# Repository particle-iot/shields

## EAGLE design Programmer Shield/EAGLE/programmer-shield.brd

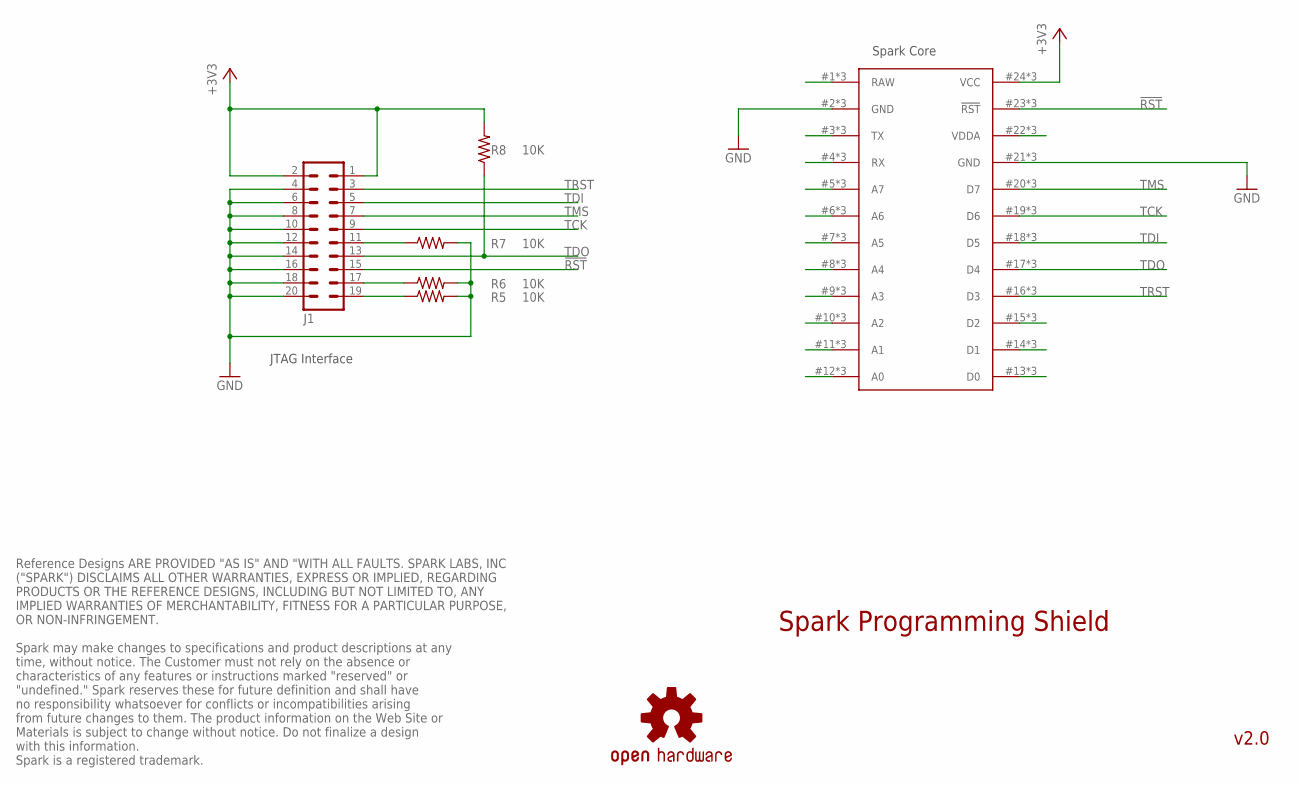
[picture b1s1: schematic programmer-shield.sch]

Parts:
J1: ML20
LOGO1: OSHW-LOGOM; OSHW-LOGO-M
R5, R6, R7, R8: 10K; AXIAL-0.3
U$1: SPARK_CORE; SPARK_CORE_STACKABLE

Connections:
!RST: J1.15, U$1.23 (!RST), U$1.#23 (!RST), U$1.@23 (!RST)
+3V3: J1.1, J1.2, R8.P$2 (2), U$1.24 (VCC), U$1.#24 (VCC), U$1.@24 (VCC)
GND: J1.4, J1.6, J1.8, J1.10, J1.12, J1.14, J1.16, J1.18, J1.20, R5.P$2 (2), R6.P$2 (2), R7.P$2 (2), U$1.2 (GND), U$1.21 (GND), U$1.#2 (GND), U$1.#21 (GND), U$1.@2 (GND), U$1.@21 (GND)
unnamed: U$1.1 (RAW), U$1.#1 (RAW), U$1.@1 (RAW)
unnamed: U$1.3 (TX), U$1.#3 (TX), U$1.@3 (TX)
unnamed: U$1.4 (RX), U$1.#4 (RX), U$1.@4 (RX)
unnamed: U$1.5 (A7), U$1.#5 (A7), U$1.@5 (A7)
unnamed: U$1.6 (A6), U$1.#6 (A6), U$1.@6 (A6)
unnamed: U$1.7 (A5), U$1.#7 (A5), U$1.@7 (A5)
unnamed: U$1.8 (A4), U$1.#8 (A4), U$1.@8 (A4)
unnamed: U$1.9 (A3), U$1.#9 (A3), U$1.@9 (A3)
unnamed: U$1.10 (A2), U$1.#10 (A2), U$1.@10 (A2)
unnamed: U$1.11 (A1), U$1.#11 (A1), U$1.@11 (A1)
unnamed: U$1.12 (A0), U$1.#12 (A0), U$1.@12 (A0)
unnamed: U$1.13 (D0), U$1.#13 (D0), U$1.@13 (D0)
unnamed: J1.19, R5.P$1 (1)
unnamed: J1.17, R6.P$1 (1)
unnamed: J1.11, R7.P$1 (1)
unnamed: U$1.14 (D1), U$1.#14 (D1), U$1.@14 (D1)
unnamed: U$1.15 (D2), U$1.#15 (D2), U$1.@15 (D2)
unnamed: U$1.22 (VDDA), U$1.#22 (VDDA), U$1.@22 (VDDA)
TCK: J1.9, U$1.19 (D6), U$1.#19 (D6), U$1.@19 (D6)
TDI: J1.5, U$1.18 (D5), U$1.#18 (D5), U$1.@18 (D5)
TDO: J1.13, R8.P$1 (1), U$1.17 (D4), U$1.#17 (D4), U$1.@17 (D4)
TMS: J1.7, U$1.20 (D7), U$1.#20 (D7), U$1.@20 (D7)
TRST: J1.3, U$1.16 (D3), U$1.#16 (D3), U$1.@16 (D3)

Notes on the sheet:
JTAG Interface
Spark Core
Spark Programming Shield
v2.0
Reference Designs ARE PROVIDED "AS IS" AND "WITH ALL FAULTS. SPARK LABS, INC ("SPARK") DISCLAIMS ALL OTHER WARRANTIES, EXPRESS OR IMPLIED, REGARDING PRODUCTS OR THE REFERENCE DESIGNS, INCLUDING BUT NOT LIMITED TO, ANY IMPLIED WARRANTIES OF MERCHANTABILITY, FITNESS FOR A PARTICULAR PURPOSE, OR NON-I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

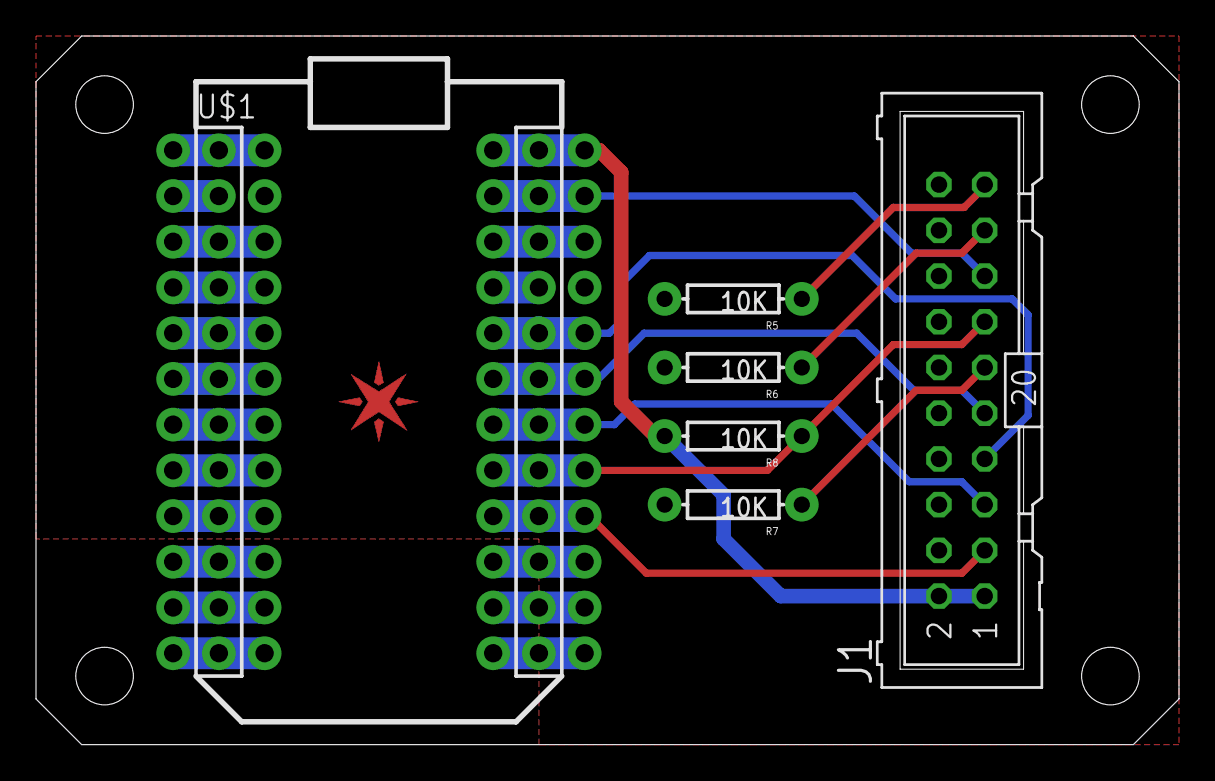
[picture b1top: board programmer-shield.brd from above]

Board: 2 copper layers, 63.5 x 39.4 mm, 8 parts (1 on the bottom side), 26 nets.

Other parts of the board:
E$1: SPARK_LOGO_PLUS_PLANE

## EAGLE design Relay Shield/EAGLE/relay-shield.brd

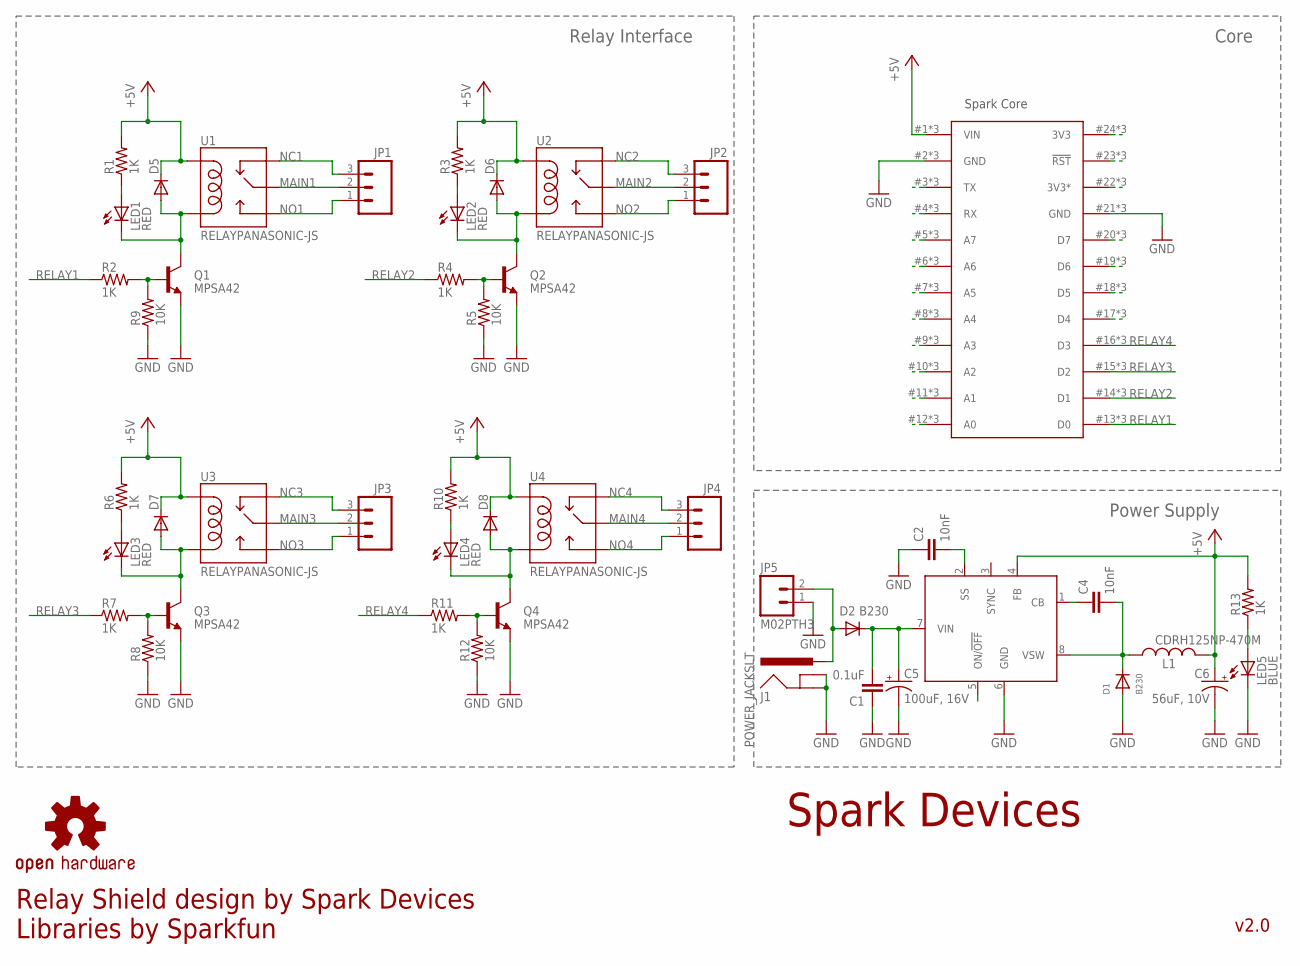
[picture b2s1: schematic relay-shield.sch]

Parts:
C1: 0.1uF; 0603-CAP
C2, C4: 10nF; 0603-CAP
C5: 100uF, 16V; PANASONIC_D
C6: 56uF, 10V; PANASONIC_D
D1, D2: B230; SMADIODE
D5, D6, D7, D8: DIODE-SOD123; SOD123
J1: POWER_JACKSLT; POWER_JACK_SLOT
JP1, JP2, JP3, JP4: M03-SCREW-5MM; SCREWTERMINAL-5MM-3
JP5: M02PTH3; 1X02_LONGPADS
L1: CDRH125NP-470M; CDRH125
LED1, LED2, LED3, LED4: RED; LED-0603
LED5: BLUE; LED-0603
LOGO1: OSHW-LOGOM; OSHW-LOGO-M
Q1, Q2, Q3, Q4: MPSA42; SOT23
R1, R2, R3, R4, R6, R7, R10, R11, R13: 1K; 0603-RES
R5, R8, R9, R12: 10K; 0603-RES
U1, U2, U3, U4: RELAYPANASONIC-JS; JS1-5V-F
U6: LM2672; SO08
U$1: SPARK_CORE; SPARK_CORE_STACKABLE

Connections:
+5V: C6.+, D5.C, D6.C, D7.C, D8.C, L1.2, R1.2, R3.2, R6.2, R10.2, R13.2, U1.COIL1, U2.COIL1, U3.COIL1, U4.COIL1, U6.4 (FB), U$1.1 (VIN), U$1.#1 (VIN), U$1.@1 (VIN)
GND: C1.1, C2.1, C5.-, C6.-, D1.A, J1.GND@1 (GNDBREAK), J1.GND@2 (GND), JP5.1, LED5.C, Q1.2 (E), Q2.2 (E), Q3.2 (E), Q4.2 (E), R5.1, R8.1, R9.1, R12.1, U6.6 (GND), U$1.2 (GND), U$1.21 (GND), U$1.#2 (GND), U$1.#21 (GND), U$1.@2 (GND), U$1.@21 (GND)
MAIN1: JP1.2, U1.COMMON (MAIN)
MAIN2: JP2.2, U2.COMMON (MAIN)
MAIN3: JP3.2, U3.COMMON (MAIN)
MAIN4: JP4.2, U4.COMMON (MAIN)
unnamed: D5.A, LED1.C, Q1.3 (C), U1.COIL2
unnamed: Q2.1 (B), R4.2, R5.2
unnamed: Q1.1 (B), R2.2, R9.2
unnamed: LED1.A, R1.1
unnamed: D6.A, LED2.C, Q2.3 (C), U2.COIL2
unnamed: LED2.A, R3.1
unnamed: Q3.1 (B), R7.2, R8.2
unnamed: D7.A, LED3.C, Q3.3 (C), U3.COIL2
unnamed: LED3.A, R6.1
unnamed: Q4.1 (B), R11.2, R12.2
unnamed: D8.A, LED4.C, Q4.3 (C), U4.COIL2
unnamed: LED4.A, R10.1
unnamed: U$1.17 (D4), U$1.#17 (D4), U$1.@17 (D4)
unnamed: C1.2, C5.+, D2.C, U6.7 (VIN)
unnamed: U$1.18 (D5), U$1.#18 (D5), U$1.@18 (D5)
unnamed: LED5.A, R13.1
unnamed: U$1.19 (D6), U$1.#19 (D6), U$1.@19 (D6)
unnamed: U$1.20 (D7), U$1.#20 (D7), U$1.@20 (D7)
unnamed: U$1.22 (3V3*), U$1.#22 (3V3*), U$1.@22 (3V3*)
unnamed: U$1.23 (!RST), U$1.#23 (!RST), U$1.@23 (!RST)
unnamed: U$1.24 (3V3), U$1.#24 (3V3), U$1.@24 (3V3)
unnamed: U$1.12 (A0), U$1.#12 (A0), U$1.@12 (A0)
unnamed: U$1.11 (A1), U$1.#11 (A1), U$1.@11 (A1)
unnamed: U$1.10 (A2), U$1.#10 (A2), U$1.@10 (A2)
unnamed: U$1.9 (A3), U$1.#9 (A3), U$1.@9 (A3)
unnamed: U$1.8 (A4), U$1.#8 (A4), U$1.@8 (A4)
unnamed: U$1.7 (A5), U$1.#7 (A5), U$1.@7 (A5)
unnamed: U$1.6 (A6), U$1.#6 (A6), U$1.@6 (A6)
unnamed: U$1.5 (A7), U$1.#5 (A7), U$1.@5 (A7)
unnamed: U$1.4 (RX), U$1.#4 (RX), U$1.@4 (RX)
unnamed: U$1.3 (TX), U$1.#3 (TX), U$1.@3 (TX)
unnamed: D2.A, J1.PWR, JP5.2
unnamed: C4.1, U6.1 (CB)
unnamed: C4.2, D1.C, L1.1, U6.8 (VSW)
unnamed: C2.2, U6.2 (SS)
NC1: JP1.3, U1.CLOSED (NC)
NC2: JP2.3, U2.CLOSED (NC)
NC3: JP3.3, U3.CLOSED (NC)
NC4: JP4.3, U4.CLOSED (NC)
NO1: JP1.1, U1.OPEN (NO)
NO2: JP2.1, U2.OPEN (NO)
NO3: JP3.1, U3.OPEN (NO)
NO4: JP4.1, U4.OPEN (NO)
RELAY1: R2.1, U$1.13 (D0), U$1.#13 (D0), U$1.@13 (D0)
RELAY2: R4.1, U$1.14 (D1), U$1.#14 (D1), U$1.@14 (D1)
RELAY3: R7.1, U$1.15 (D2), U$1.#15 (D2), U$1.@15 (D2)
RELAY4: R11.1, U$1.16 (D3), U$1.#16 (D3), U$1.@16 (D3)

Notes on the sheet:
Spark Core
Spark Devices
Core
Relay Interface
Power Supply
Relay Shield design by Spark Devices Libraries by Sparkfun
v2.0

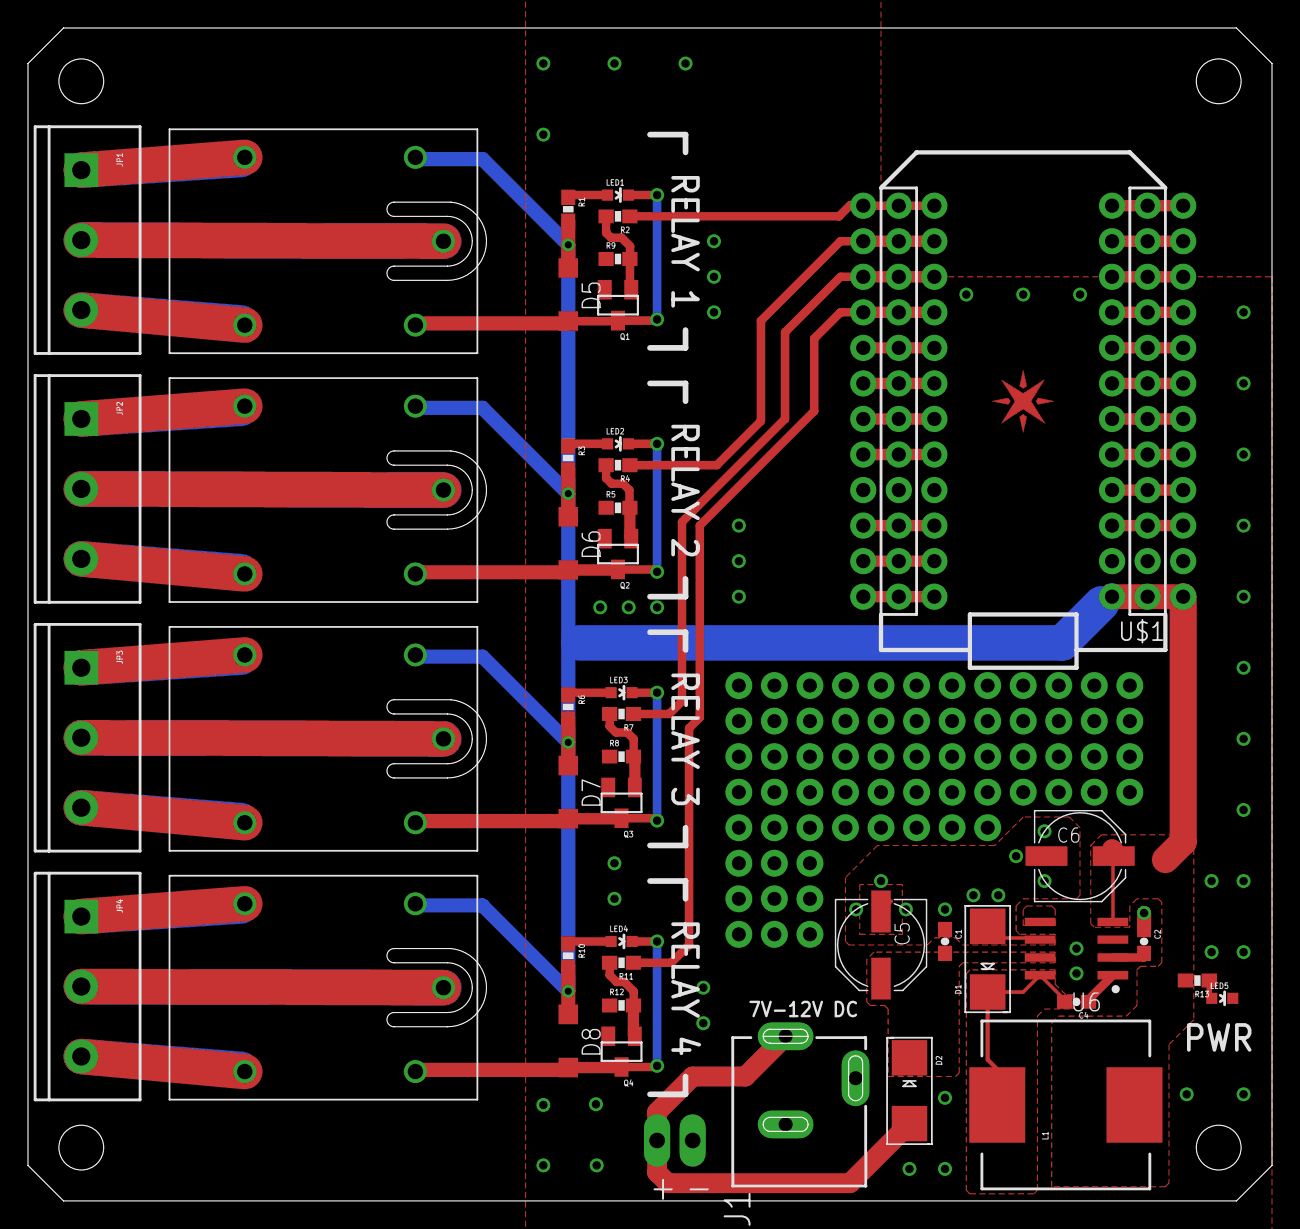
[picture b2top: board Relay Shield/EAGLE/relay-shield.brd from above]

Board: 2 copper layers, 88.9 x 83.8 mm, 48 parts (1 on the bottom side), 53 nets.

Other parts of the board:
E$1: SPARK_LOGO_PLUS_PLANE

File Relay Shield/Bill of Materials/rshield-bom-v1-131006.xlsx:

| PROJECT NAME |  | SPARK RELAY SHIELD
 | LAST UPDATED |  | 41553
 | RSHIELD
 | Qty | AQS P/N | Device | Minimum Specification | Component Value (if different) | Package/Case | Designator | AVL | AVL P/N | Additional Comments
 | 1 | 307-20-301623 | Fab PCB | Single Sided, 1.6mm, 1OZ, Electroless Nickel Immersion Gold, White Solder Mask,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 |  |  |  |  |  | CONSIGNED BY SPARK
 | 1 | HL-121-08-301869 | Capacitor | 10nF, 10%, 10V |  | 0603 | C4 | AVX | 0603ZC103KAT2A
 | 2 | HL-201-40-101081 | Diode | 30V, 2A |  | DO-214 | D1, D2 | Diodes, Inc. | B230A-13-F
 | 4 | HL-201-50-301081 | Diode | 0.15A |  | SOD123 | D5-D8 | Arrow | 1N4148
 | 2 | HL-515-30-301994 | Female Header | Single String, 0.230" Mating Length |  | 0.1", 12 pin | JP5, JP6 | Kaweei | CS25401-12G-S85-C 
 | 1 | HL-161-53-301137 | Inductor | 47uH Power Inductor, SMD |  | 12.7mm x 10mm | L1 | Bourns, Inc. | SDR1005-470KL
 | 1 |  | LED | Blue |  | 0603 | LED5 | Wenliang | WLUB0603A-341
 | 4 | HL-414-10-301296 | LED | Red |  | 0603 | LED1-LED4 | Wenliang | WLUE0603A-25
 | 4 | HL-211-60-301212 | NPN Transistor | 300V |  | SOT23 | Q1-Q4 | Micro Commercial | MMBTA42-TP
 | 1 | HL-121-36-301178 | Polarized Capacitor | 100uF, 10V, 20% |  | 6.3mm diameter, SMT | C6 | Panasonic Electronic Components | EEE-1AA101SP
 | 1 | HL-121-64-301147 | Polarized Capacitor | 47uF, 25V, 20% |  | 6.3mm diameter, SMT | C5 | Panasonic Electronic Components | EEE-1EA470WP
 | 1 | HL-515-50-301064 | Power Barrel Jack Connector |  |  | Through-hole, 3 contacts | J1 | Kaweei | TDC-005-20
 | 4 | HL-105-10-301382 | Resistor | 10K, 1/4W, 5% |  | 0603 | R5, R8, R9, R12 | Rohm Semiconductor | ESR03EZPJ103
 | 9 | HL-101-15-303050 | Resistor | 1K, 1/4W, 5% |  | 0603 | R1-R4, R6-R7, R10-R11, R13 | Rohm Semiconductor | ESR03EZPJ102
 | 4 | HL-511-30-301384 | Screw Terminal | M03, 10A, green |  | 5mm pitch, 3 pin | JP1, JP2, JP3, JP4 | Boda | PA001-5.0-3P
 | 4 | 418-20-301016 | SPDT Relay | 10A, 250VAC/25VDC |  | COM-00101 | U1-U4 | Verical | JS1-5V-F | CONSIGNED BY SPARK
 | 1 | HL-221-28-301648 | Voltage Regulator | Buck Regulator, 5V, 2A |  | 8-SOP | U6 | Diodes, Inc. | AP1509-50SG-13
 | PACKAGING
 | Qty |  | Device | Minimum Specification | Component Value (if different) | Package/Case | Designator | AVL | AVL P/N | Additional Comments
 | 1 | HL-901-00-301328 | Large Static Bag |  |  | 160 x 130mm
 | 1 | HL-901-00-301333 | Large Static Bubble Bag |  |  | 170 x 140mm, red
 | 1 | 831-10-301390 | "STICK-RS" sticker | Shield Description and UPC Barcode |  | 8 x 10 cm |  |  |  | CONSIGNED BY SPARK

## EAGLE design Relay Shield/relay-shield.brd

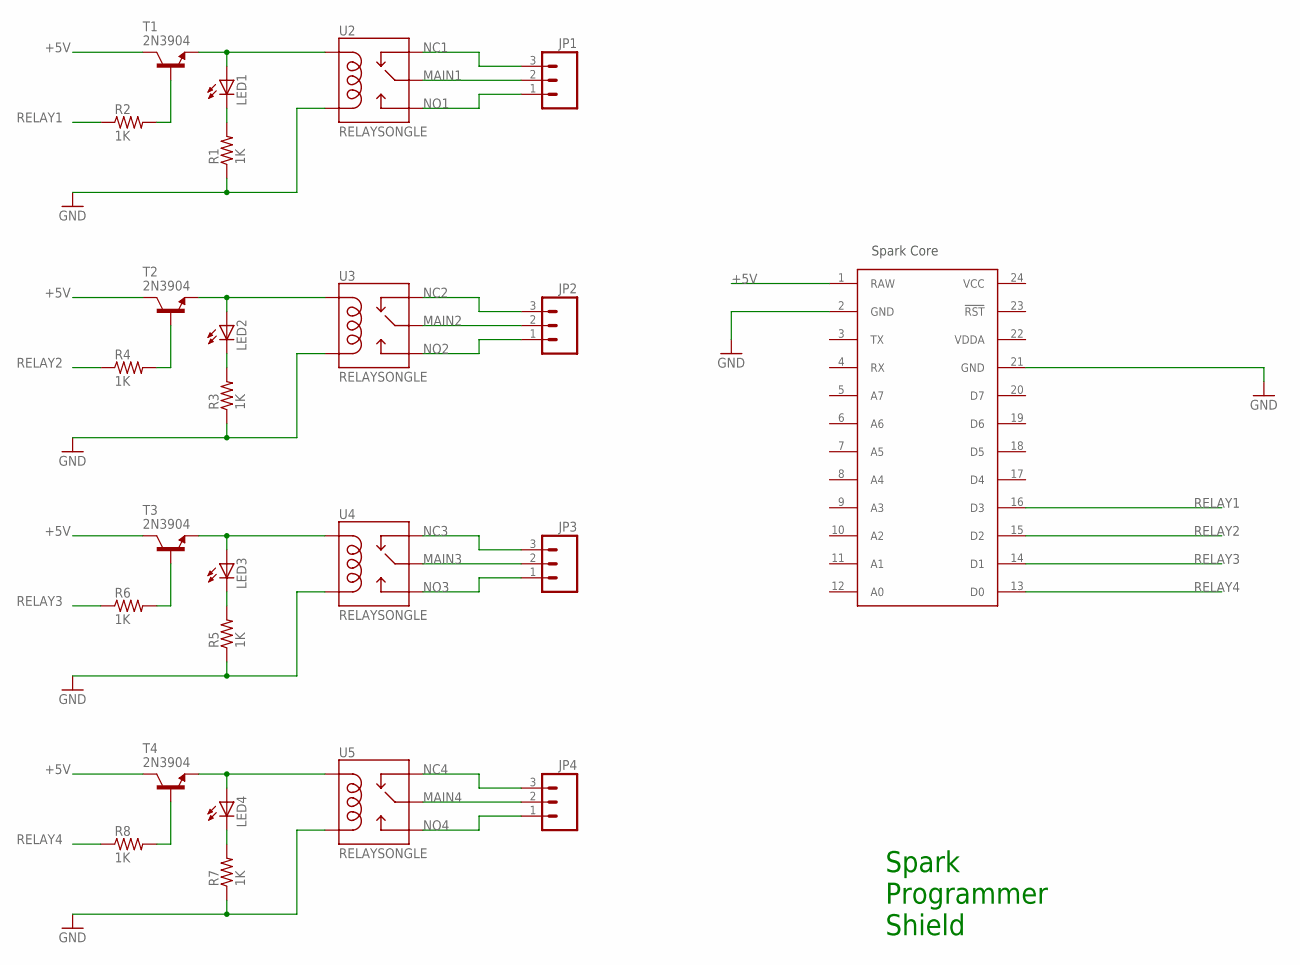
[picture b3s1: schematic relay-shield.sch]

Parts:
JP1, JP2, JP3, JP4: M03-SCREW-5MM; SCREWTERMINAL-5MM-3
LED1, LED2, LED3, LED4: LED3MM
R1, R2, R3, R4, R5, R6, R7, R8: 1K; AXIAL-0.3
T1, T2, T3, T4: 2N3904; TO92
U1: SPARK_CORECORE; SPARK_CORE
U2, U3, U4, U5: RELAYSONGLE; SRD-5VDC-SL-C

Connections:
+5V: T1.1 (C), T2.1 (C), T3.1 (C), T4.1 (C), U1.1 (RAW)
GND: R1.P$1 (1), R3.P$1 (1), R5.P$1 (1), R7.P$1 (1), U1.2 (GND), U1.21 (GND), U2.COIL2, U3.COIL2, U4.COIL2, U5.COIL2
MAIN1: JP1.2, U2.COMMON (MAIN)
MAIN2: JP2.2, U3.COMMON (MAIN)
MAIN3: JP3.2, U4.COMMON (MAIN)
MAIN4: JP4.2, U5.COMMON (MAIN)
unnamed: LED1.A, T1.3 (E), U2.COIL1
unnamed: LED2.A, T2.3 (E), U3.COIL1
unnamed: R2.P$2 (2), T1.2 (B)
unnamed: LED1.K (C), R1.P$2 (2)
unnamed: R4.P$2 (2), T2.2 (B)
unnamed: LED2.K (C), R3.P$2 (2)
unnamed: LED3.A, T3.3 (E), U4.COIL1
unnamed: R6.P$2 (2), T3.2 (B)
unnamed: LED3.K (C), R5.P$2 (2)
unnamed: LED4.A, T4.3 (E), U5.COIL1
unnamed: R8.P$2 (2), T4.2 (B)
unnamed: LED4.K (C), R7.P$2 (2)
NC1: JP1.3, U2.CLOSED (NC)
NC2: JP2.3, U3.CLOSED (NC)
NC3: JP3.3, U4.CLOSED (NC)
NC4: JP4.3, U5.CLOSED (NC)
NO1: JP1.1, U2.OPEN (NO)
NO2: JP2.1, U3.OPEN (NO)
NO3: JP3.1, U4.OPEN (NO)
NO4: JP4.1, U5.OPEN (NO)
RELAY1: R2.P$1 (1), U1.16 (D3)
RELAY2: R4.P$1 (1), U1.15 (D2)
RELAY3: R6.P$1 (1), U1.14 (D1)
RELAY4: R8.P$1 (1), U1.13 (D0)
VCC: U1.24 (VCC)
VDDA: U1.22 (VDDA)

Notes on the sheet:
Spark Core
Spark Programmer Shield

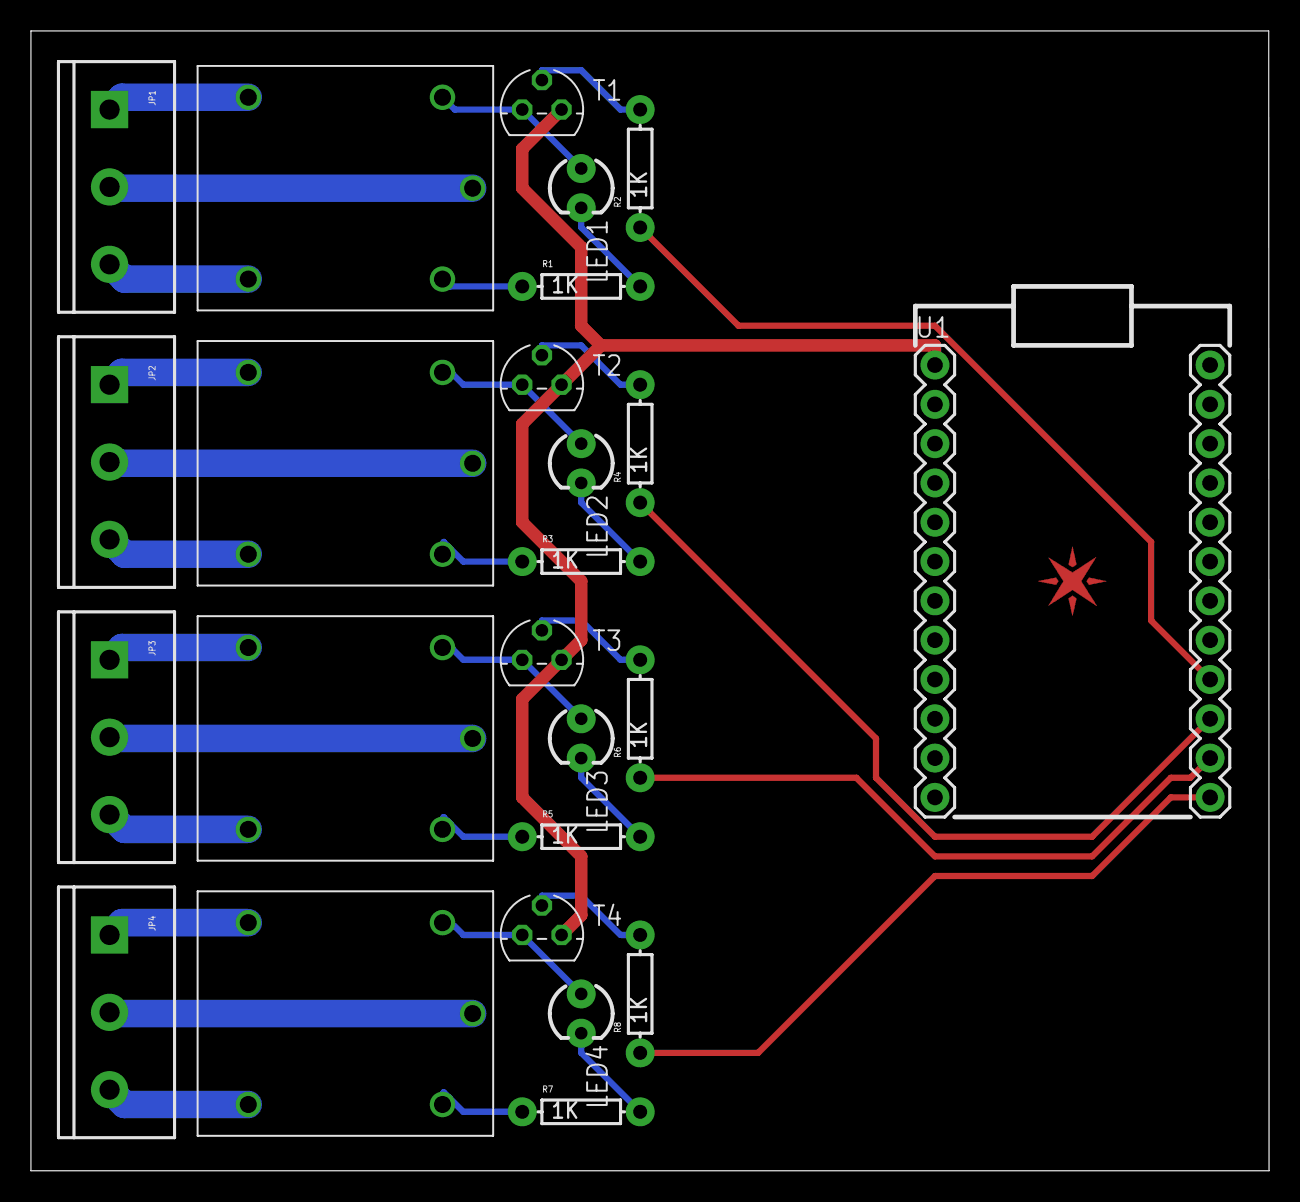
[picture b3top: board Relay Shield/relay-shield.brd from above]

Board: 2 copper layers, 80.0 x 73.7 mm, 26 parts (0 on the bottom side), 30 nets.

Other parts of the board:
E$1: SPARK_LOGO_PLUS_PLANE

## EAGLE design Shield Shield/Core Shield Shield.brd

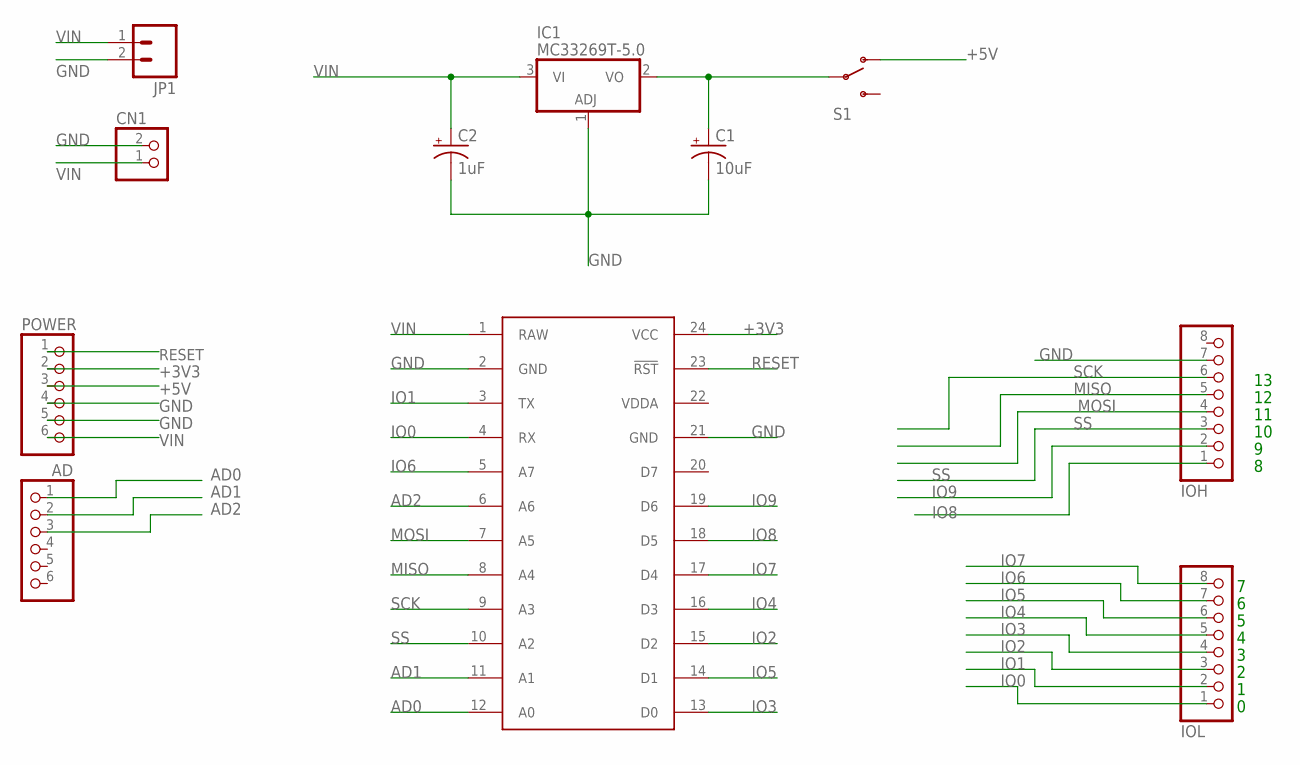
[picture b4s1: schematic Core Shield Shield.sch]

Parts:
AD: PINHD-1X6; 1X06
C1: 10uF; CPOL-RADIAL-10UF-25V
C2: 1uF; CPOL-RADIAL-10UF-25V
CN1: JST_2PIN-THM; JST-PH-2-THM
IC1: MC33269T-5.0; TO220V
IOH: PINHD-1X8; 1X08
IOL: PINHD-1X8; 1X08
JP1: M02LOCK; 1X02_LOCK
POWER: PINHD-1X6; 1X06
S1: SWITCH-SPDTPTH; SWITCH-SPDT
U$1: SPARK_CORECORE; SPARK_CORE

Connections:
+3V3: POWER.2, U$1.24 (VCC)
+5V: POWER.3, S1.1 (O)
AD0: AD.1, U$1.12 (A0)
AD1: AD.2, U$1.11 (A1)
AD2: AD.3, U$1.6 (A6)
GND: C1.2 (-), C2.2 (-), CN1.2 (1), IC1.1 (ADJ), IOH.7, JP1.2, POWER.4, POWER.5, U$1.2 (GND), U$1.21 (GND)
IO0: IOL.1, U$1.4 (RX)
IO1: IOL.2, U$1.3 (TX)
IO2: IOL.3, U$1.15 (D2)
IO3: IOL.4, U$1.13 (D0)
IO4: IOL.5, U$1.16 (D3)
IO5: IOL.6, U$1.14 (D1)
IO6: IOL.7, U$1.5 (A7)
IO7: IOL.8, U$1.17 (D4)
IO8: IOH.1, U$1.18 (D5)
IO9: IOH.2, U$1.19 (D6)
MISO: IOH.5, U$1.8 (A4)
MOSI: IOH.4, U$1.7 (A5)
N1: C1.1 (+), IC1.2 (VO), S1.2
RESET: POWER.1, U$1.23 (!RST)
SCK: IOH.6, U$1.9 (A3)
SS: IOH.3, U$1.10 (A2)
VDDA: U$1.22 (VDDA)
VIN: C2.1 (+), CN1.1 (2), IC1.3 (VI), JP1.1, POWER.6, U$1.1 (RAW)

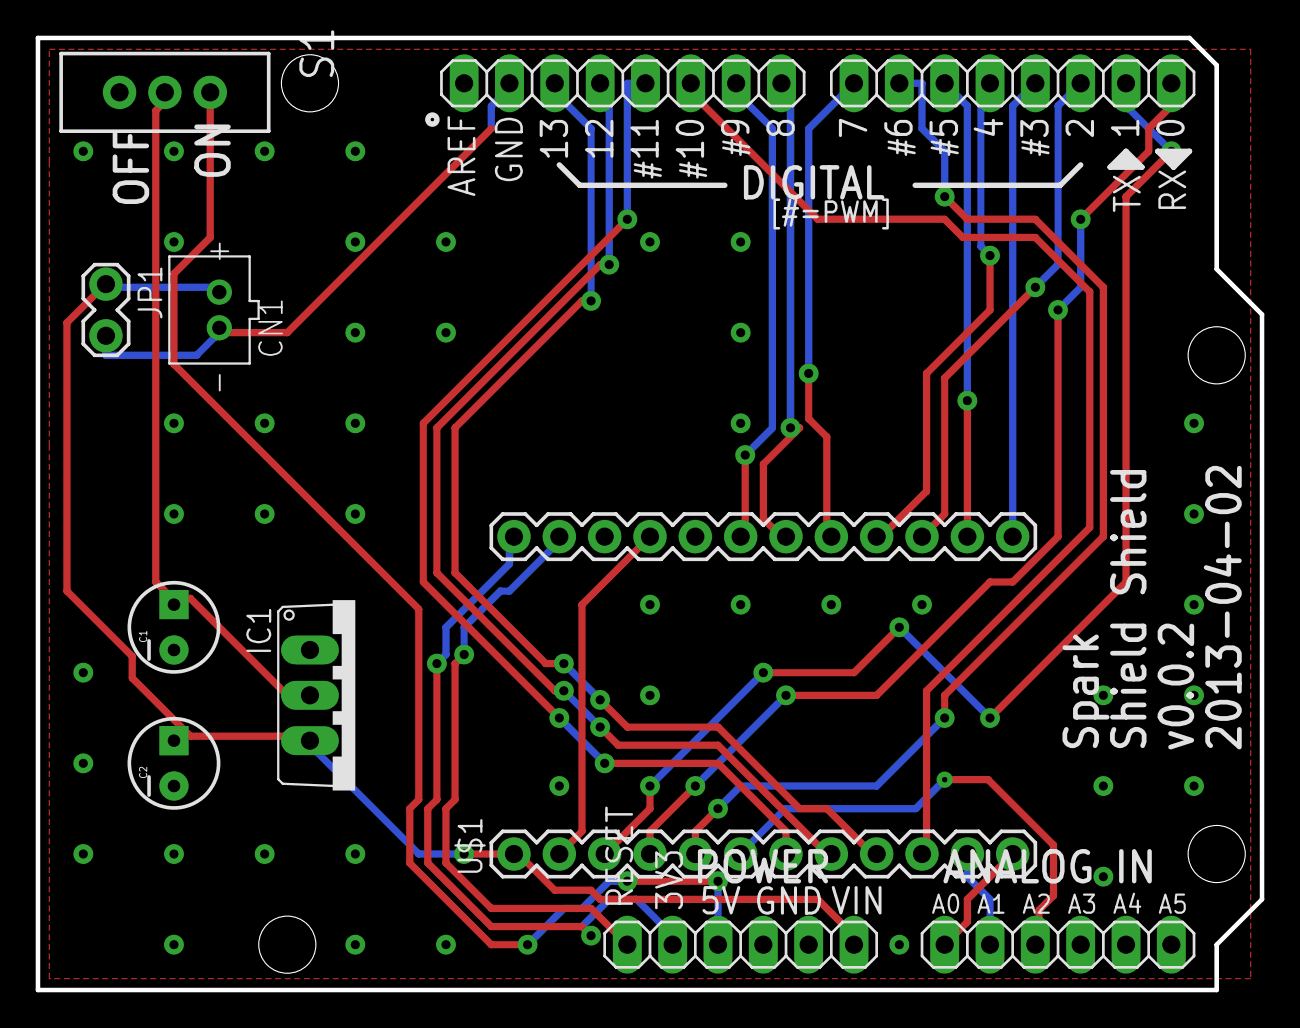
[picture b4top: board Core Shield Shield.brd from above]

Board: 2 copper layers, 68.6 x 53.3 mm, 12 parts (0 on the bottom side), 23 nets.

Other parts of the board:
U$2: SPARK_LOGO

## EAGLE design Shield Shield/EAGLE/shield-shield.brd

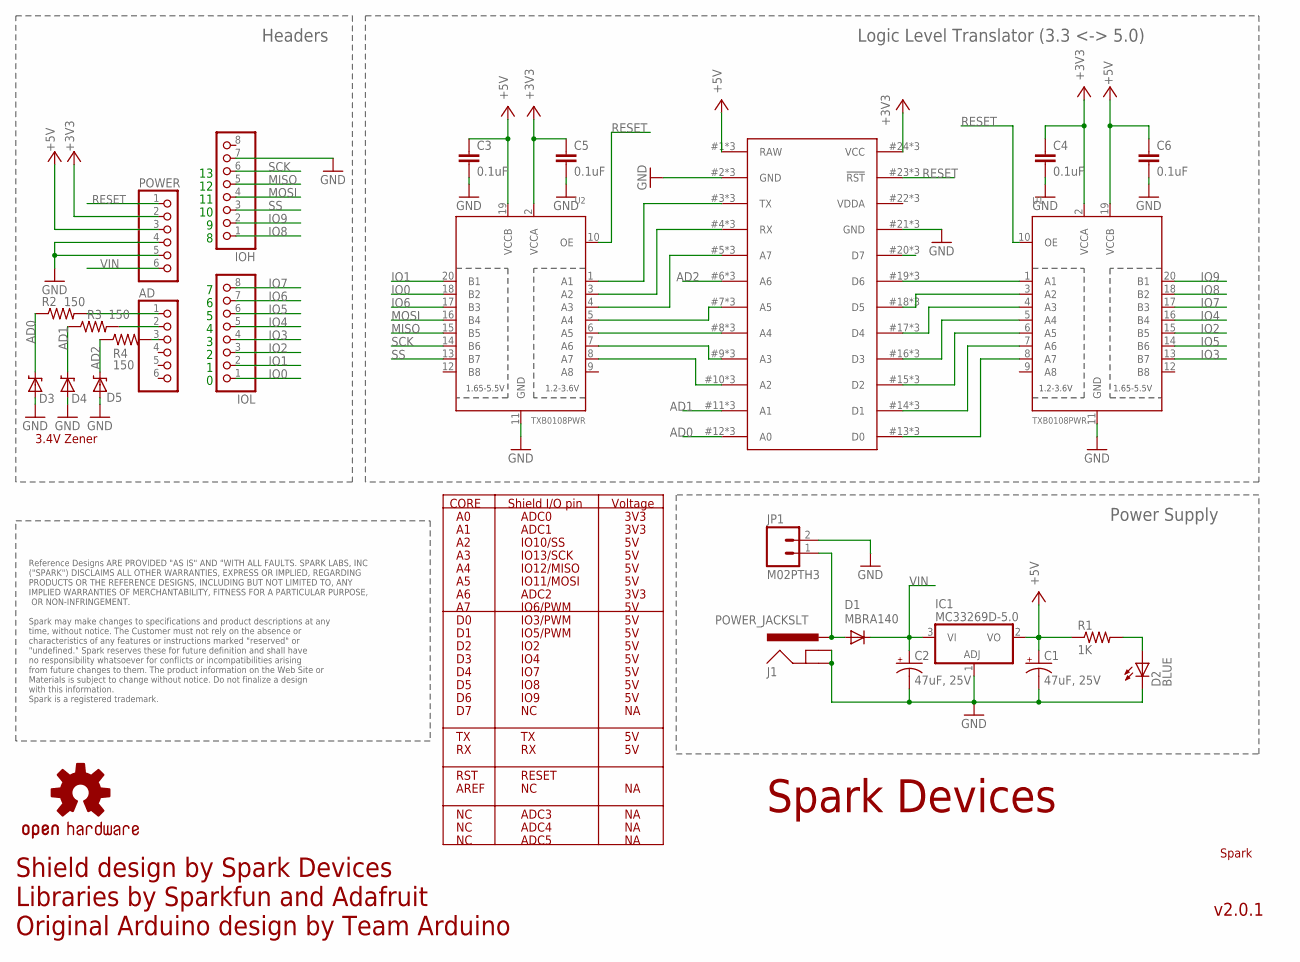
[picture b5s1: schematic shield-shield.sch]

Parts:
AD: 6 pin female header; 1X06
C1, C2: 47uF, 25V; PANASONIC_D
C3, C4, C5, C6: 0.1uF; C0603
D1: MBRA140; SMA-DIODE
D2: BLUE; LED-1206
D3, D4, D5: DIODE-ZENER-BZT52; SOD-323
IC1: MC33269D-5.0; DPACK
IOH: 8 pin female header; 1X08
IOL: 8 pin female header; 1X08
J1: POWER_JACKSLT; POWER_JACK_SLOT
JP1: M02PTH3; 1X02_LONGPADS
LOGO1: OSHW-LOGOM; OSHW-LOGO-M
POWER: 6 pin female header; 1X06
R1: 1K; 0603-RES
R2, R3, R4: 150; 0603-RES
U1, U2: TXB0108PWR; TSSOP20
U$1: SPARK_CORE; SPARK_CORE_STACKABLE
U$3: SPARK_LOGO; SPARK_LOGO_TSTOP

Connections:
+3V3: C4.1, C5.1, POWER.2, U1.2 (VCCA), U2.2 (VCCA), U$1.24 (VCC), U$1.#24 (VCC), U$1.@24 (VCC)
+5V: C1.+, C3.1, C6.1, IC1.2 (VO), POWER.3, R1.1, U1.19 (VCCB), U2.19 (VCCB), U$1.1 (RAW), U$1.#1 (RAW), U$1.@1 (RAW)
A2: U2.8 (A7), U$1.10 (A2), U$1.#10 (A2), U$1.@10 (A2)
A3: U2.7 (A6), U$1.9 (A3), U$1.#9 (A3), U$1.@9 (A3)
A4: U2.6 (A5), U$1.8 (A4), U$1.#8 (A4), U$1.@8 (A4)
A5: U2.5 (A4), U$1.7 (A5), U$1.#7 (A5), U$1.@7 (A5)
A7: U2.4 (A3), U$1.5 (A7), U$1.#5 (A7), U$1.@5 (A7)
AD0: D3.1 (C), R2.1, U$1.12 (A0), U$1.#12 (A0), U$1.@12 (A0)
AD1: D4.1 (C), R3.1, U$1.11 (A1), U$1.#11 (A1), U$1.@11 (A1)
AD2: D5.1 (C), R4.1, U$1.6 (A6), U$1.#6 (A6), U$1.@6 (A6)
D7: U$1.20 (D7), U$1.#20 (D7), U$1.@20 (D7)
GND: C1.-, C2.-, C3.2, C4.2, C5.2, C6.2, D2.C, D3.2 (A), D4.2 (A), D5.2 (A), IC1.1 (ADJ), IOH.7, J1.GND@1 (GNDBREAK), J1.GND@2 (GND), JP1.2, POWER.4, POWER.5, U1.11 (GND), U2.11 (GND), U$1.2 (GND), U$1.21 (GND), U$1.#2 (GND), U$1.#21 (GND), U$1.@2 (GND), U$1.@21 (GND)
IO0: IOL.1, U2.18 (B2)
IO1: IOL.2, U2.20 (B1)
IO2: IOL.3, U1.15 (B5)
IO3: IOL.4, U1.13 (B7)
IO4: IOL.5, U1.16 (B4)
IO5: IOL.6, U1.14 (B6)
IO6: IOL.7, U2.17 (B3)
IO7: IOL.8, U1.17 (B3)
IO8: IOH.1, U1.18 (B2)
IO9: IOH.2, U1.20 (B1)
MISO: IOH.5, U2.15 (B5)
MOSI: IOH.4, U2.16 (B4)
unnamed: U1.1 (A1), U$1.19 (D6), U$1.#19 (D6), U$1.@19 (D6)
unnamed: U1.3 (A2), U$1.18 (D5), U$1.#18 (D5), U$1.@18 (D5)
unnamed: U1.4 (A3), U$1.17 (D4), U$1.#17 (D4), U$1.@17 (D4)
unnamed: U1.5 (A4), U$1.16 (D3), U$1.#16 (D3), U$1.@16 (D3)
unnamed: U1.6 (A5), U$1.15 (D2), U$1.#15 (D2), U$1.@15 (D2)
unnamed: U1.7 (A6), U$1.14 (D1), U$1.#14 (D1), U$1.@14 (D1)
unnamed: U1.8 (A7), U$1.13 (D0), U$1.#13 (D0), U$1.@13 (D0)
unnamed: D1.A, J1.PWR, JP1.1
unnamed: D2.A, R1.2
unnamed: AD.1, R2.2
unnamed: AD.2, R3.2
unnamed: AD.3, R4.2
RESET: POWER.1, U1.10 (OE), U2.10 (OE), U$1.23 (!RST), U$1.#23 (!RST), U$1.@23 (!RST)
RX: U2.3 (A2), U$1.4 (RX), U$1.#4 (RX), U$1.@4 (RX)
SCK: IOH.6, U2.14 (B6)
SS: IOH.3, U2.13 (B7)
TX: U2.1 (A1), U$1.3 (TX), U$1.#3 (TX), U$1.@3 (TX)
VDDA: U$1.22 (VDDA), U$1.#22 (VDDA), U$1.@22 (VDDA)
VIN: C2.+, D1.C, IC1.3 (VI), POWER.6

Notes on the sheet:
Spark Devices
Power Supply
Logic Level Translator (3.3 <-> 5.0)
Headers
Shield design by Spark Devices Libraries by Sparkfun and Adafruit Original Arduino design by Team Arduino
CORE
Shield I/O pin
ADC0
ADC1
IO10/SS
IO13/SCK
IO12/MISO
IO11/MOSI
ADC2
IO6/PWM
IO3/PWM
IO5/PWM
IO2
IO4
IO7
IO8
IO9
ADC3
ADC4
ADC5
Voltage
3V3
RST
RESET
AREF
3.4V Zener
v2.0.1
Reference Designs ARE PROVIDED "AS IS" AND "WITH ALL FAULTS. SPARK LABS, INC ("SPARK") DISCLAIMS ALL OTHER WARRANTIES, EXPRESS OR IMPLIED, REGARDING PRODUCTS OR THE REFERENCE DESIGNS, INCLUDING BUT NOT LIMITED TO, ANY IMPLIED WARRANTIES OF MERCHANTABILITY, FITNESS FOR A PARTICULAR PURPOSE, OR NON-I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

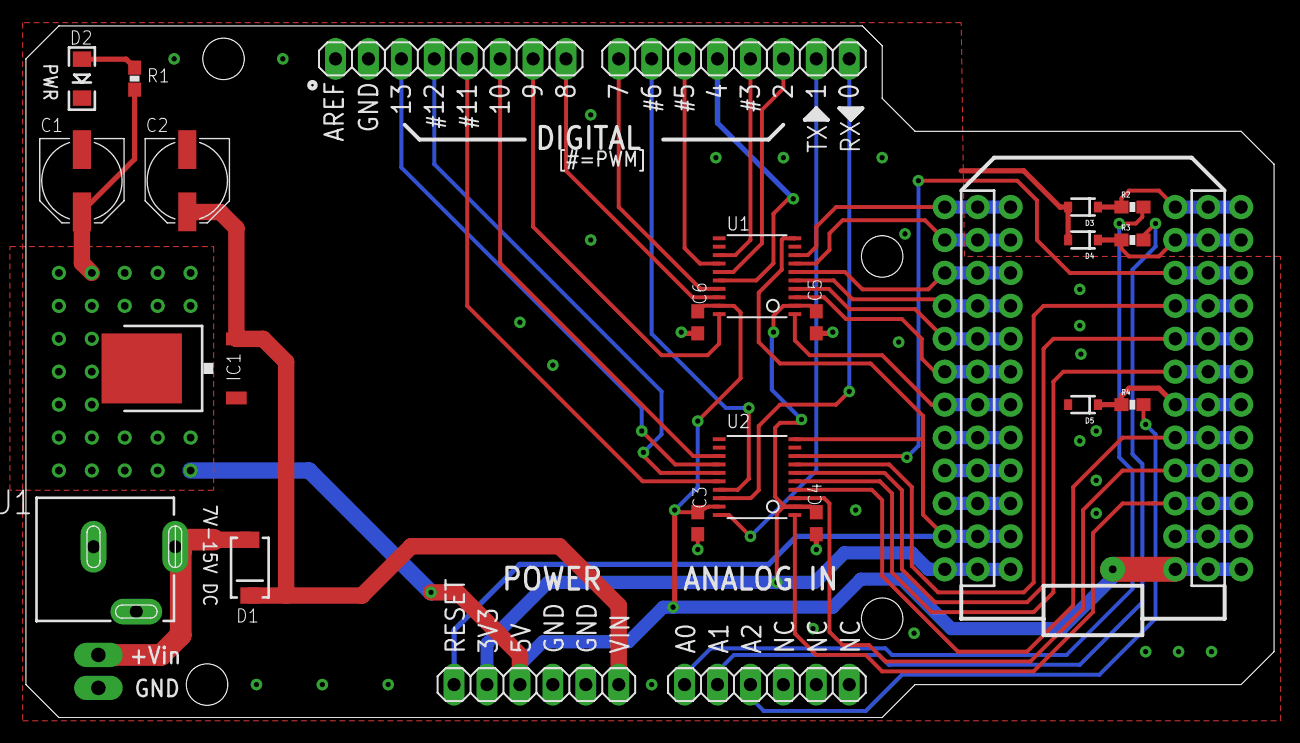
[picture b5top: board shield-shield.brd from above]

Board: 2 copper layers, 96.3 x 53.3 mm, 27 parts (1 on the bottom side), 43 nets.

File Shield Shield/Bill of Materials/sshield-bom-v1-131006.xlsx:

| PROJECT NAME |  | SPARK SHIELD SHIELD
 | LAST UPDATED |  | 41554
 | SSHIELD
 | Qty | AQS P/N | Device | Minimum Specification | Component Value (if different) | Package/Case | Designator | AVL | AVL P/N | Additional Comments
 | 1 | 307-20-301624 | Fab PCB | Single Sided, 1.6mm, 1OZ, Electroless Nickel Immersion Gold, White Solder Mask,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 |  |  |  |  |  | CONSIGNED BY SPARK
 | 2 | HL-515-30-301994 | Female Header | Single String, 0.230" Mating Length |  | 0.1", 12 pin | JP2, JP3 | KAWEEI | CS25401-12G-S85-C 
 | 2 | HL-515-30-301995 | Female Header | Single String, 0.230" Mating Length |  | 0.1", 6 pin | AD, POWER | KAWEEI | CS25401-06G-S85-C 
 | 1 | HL-414-10-301293 | LED | Blue |  | 1206 | D2 |  | WLUB1206A-341
 | 2 | HL-515-40-301740 | Female Header | Single String, 0.230" Mating Length |  | 0.1", 8 pin | IOH, IOL | KAWEEI | CS25401-08G-S85-C 
 | 1 | HL-515-50-301064 | Power Barrel Jack Connector |  |  | Through-hole, 3 contacts | J1 | KAWEEI | TDC-005-20
 | 2 | HL-121-64-301147 | Polarized Capacitor | 47uF, 25V, 20% |  | 6.3mm (0.248") diameter, SMT | C1, C2 |  | RVT1E047M0605
 | 4 | HL-121-08-301861 | Ceramic Capacitor | 0.1uF, 10%, 10V |  | 0603 | C3-C6 |  | 0603B104K01A
 | 1 | HL-101-15-303042 | Resistor | 1K, 5%, 1/10W |  | 0603 | R1 |  | 0603WAJTCE
 | 2 | HL-221-54-301299 | Bi-Directional Level Shifter | 8-Bit, 15KV ESD 20TSSOP |  | 20-TSSOP | U1, U2 | Texas Instruments | TXB0108PWR
 | 1 | HL-201-40-301080 | Diode Schottky | 40V, 1A, 550mV |  | DO-214AC (SMA) | D1 | ON Semiconductor | MBRA140T3G
 | 3 | HL-101-15-303056 | Resistor | 150R, 5%, 1/10W |  | 0603 | R2-R4 | Rohm Semiconductor | MCR03EZPEJ151
 | 3 | HL-201-55-301061 | Zener Diode | 3.4V, 500mW |  | SOD-323 | D3, D4, D5 | NXP Semiconductors | BZX84J-C3V3,115
 | 1 | HL-221-08-301035 | Voltage Regulator | LDO, 5V, 0.8A |  | DPACK (2 Leads, 1 Tab) | IC1 | ST Microelectronics | LD1117DT50CTR
 | PACKAGING
 | Qty |  | Device | Minimum Specification | Component Value (if different) | Package/Case | Designator | AVL | AVL P/N | Additional Comments
 | 1 | HL-901-00-301328 | Large Static Bag |  |  | 160 x 130mm
 | 1 | HL-901-00-301333 | Large Static Bubble Bag |  |  | 170 x 140mm, red
 | 1 | 831-10-301391 | "STICK-SS" sticker | Shield Description and UPC Barcode |  | 8 x 10 cm |  |  |  | CONSIGNED BY SPARK

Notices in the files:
parts and their libraries:
SparkFun-Passives: Licensing: CC v3.0 Share-Alike You are welcome to use this library for commercial purposes.
